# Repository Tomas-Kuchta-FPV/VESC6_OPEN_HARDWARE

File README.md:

# VESC6_OPEN_HARDWARE
> WiP Stage: Designed (asked for funding)  
Open source powerfull VESC that has 2 channels and it's based on the VESC 6 schematic.  

## Design
* 2 channels connected through CAN
* 4 layered PCB
* Continuous current: 70A per ch; instantaneous current: 120A (With proper heat sinking)
* STL130N6F7 MOSFETs rated to switch up to 130A, software limits it to 120A.
* Voltage: 10V-60V(Cells: 3-13S)
* Ports: USB-C, CAN x2, ADC, on/off switch, SWD, Hall Sensors
* LSM6DS3 IMU
* JST-SH connectors (6pin and 4 pin)
* Holes either side of the MOSFETs allow for even clamping of a simple rectangular heatsink.

Possible future upgrades with built in ESP for VESC express.  

## Manufacture
* Commonly usable and easy to source components so you can either have JLCPCB make it for you or assemble it youself.
* Custom board software build as well as hardware configuration files are available in the software folder.
  * Further testing required once I assemble it

## Credits
https://github.com/craigg96/VESC6_OPEN_HARDWARE  

## Motivation
So I love hoverboard motors, but it turns up that a lot of the ESCs are not compatible with the custom FW. And at the end of summer holidays I've designed Hover Cruiser. It's an electric skateboard made out of hoverboard motors. And also my brother made his own gocart powered by hoverboard motors. So thats why I made this modification for 2 channels.  

## BOM
| Item                       | Price          |
| -------------------------- | -------------- |
| LCSC                       | $114.67        |
| LCSC Shipping              | $13.24         |
| LCSC Tarif                 | $38.85         |
| JLCPCB                     | $38.42         |
| JLCPCB Shipping            | $11.86         |
| JLCPCB tarif               | $21.76         |
| Assembly & other materials | Freeeee labor! |
| Total                      | $238.80        |

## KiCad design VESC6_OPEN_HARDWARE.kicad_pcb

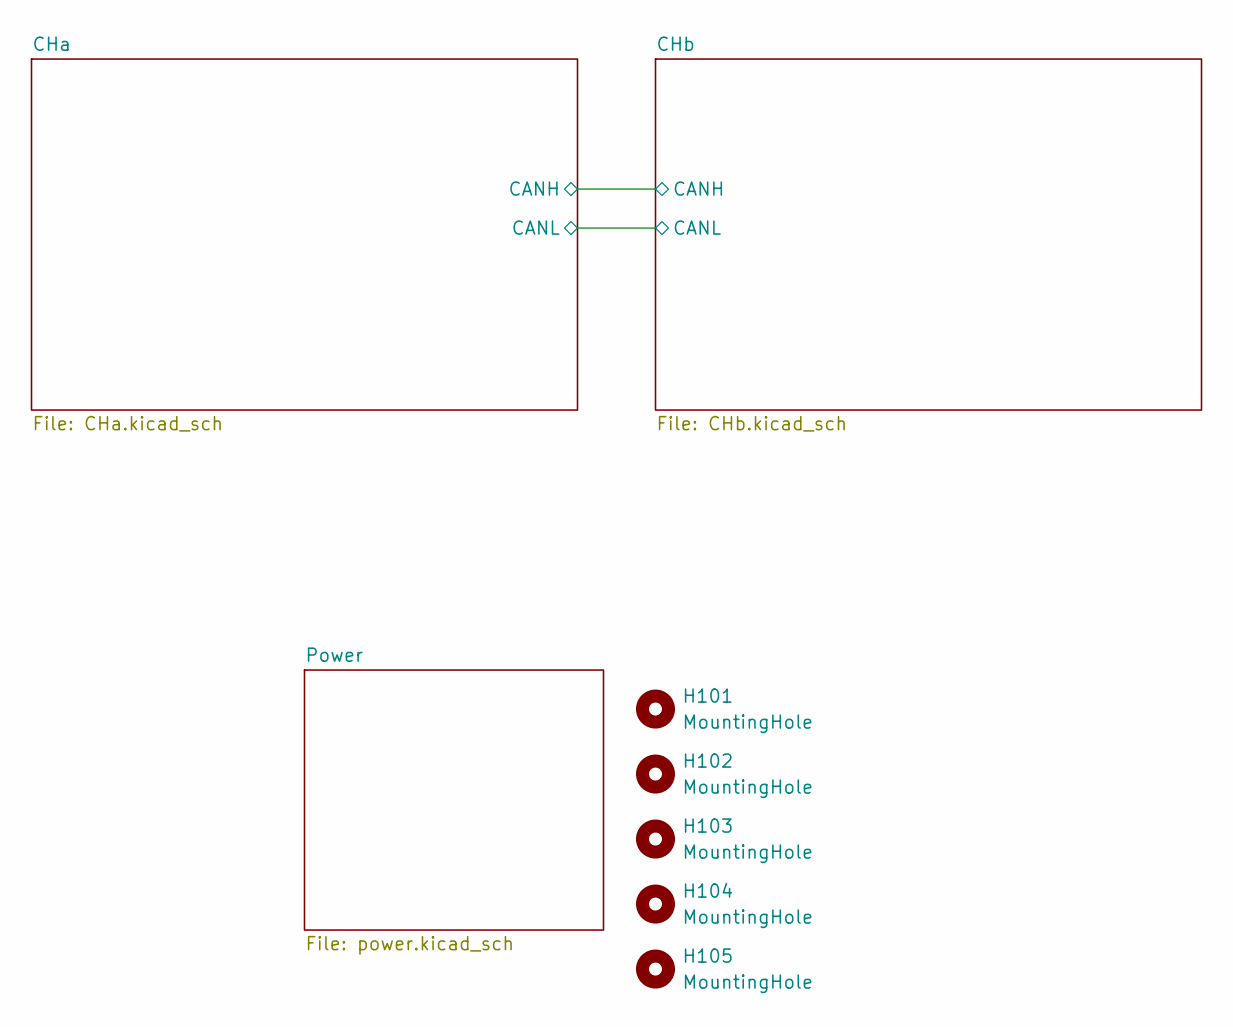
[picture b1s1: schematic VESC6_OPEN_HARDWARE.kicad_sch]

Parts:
H101, H102, H103, H104, H105: MountingHole; MountingHole_3mm

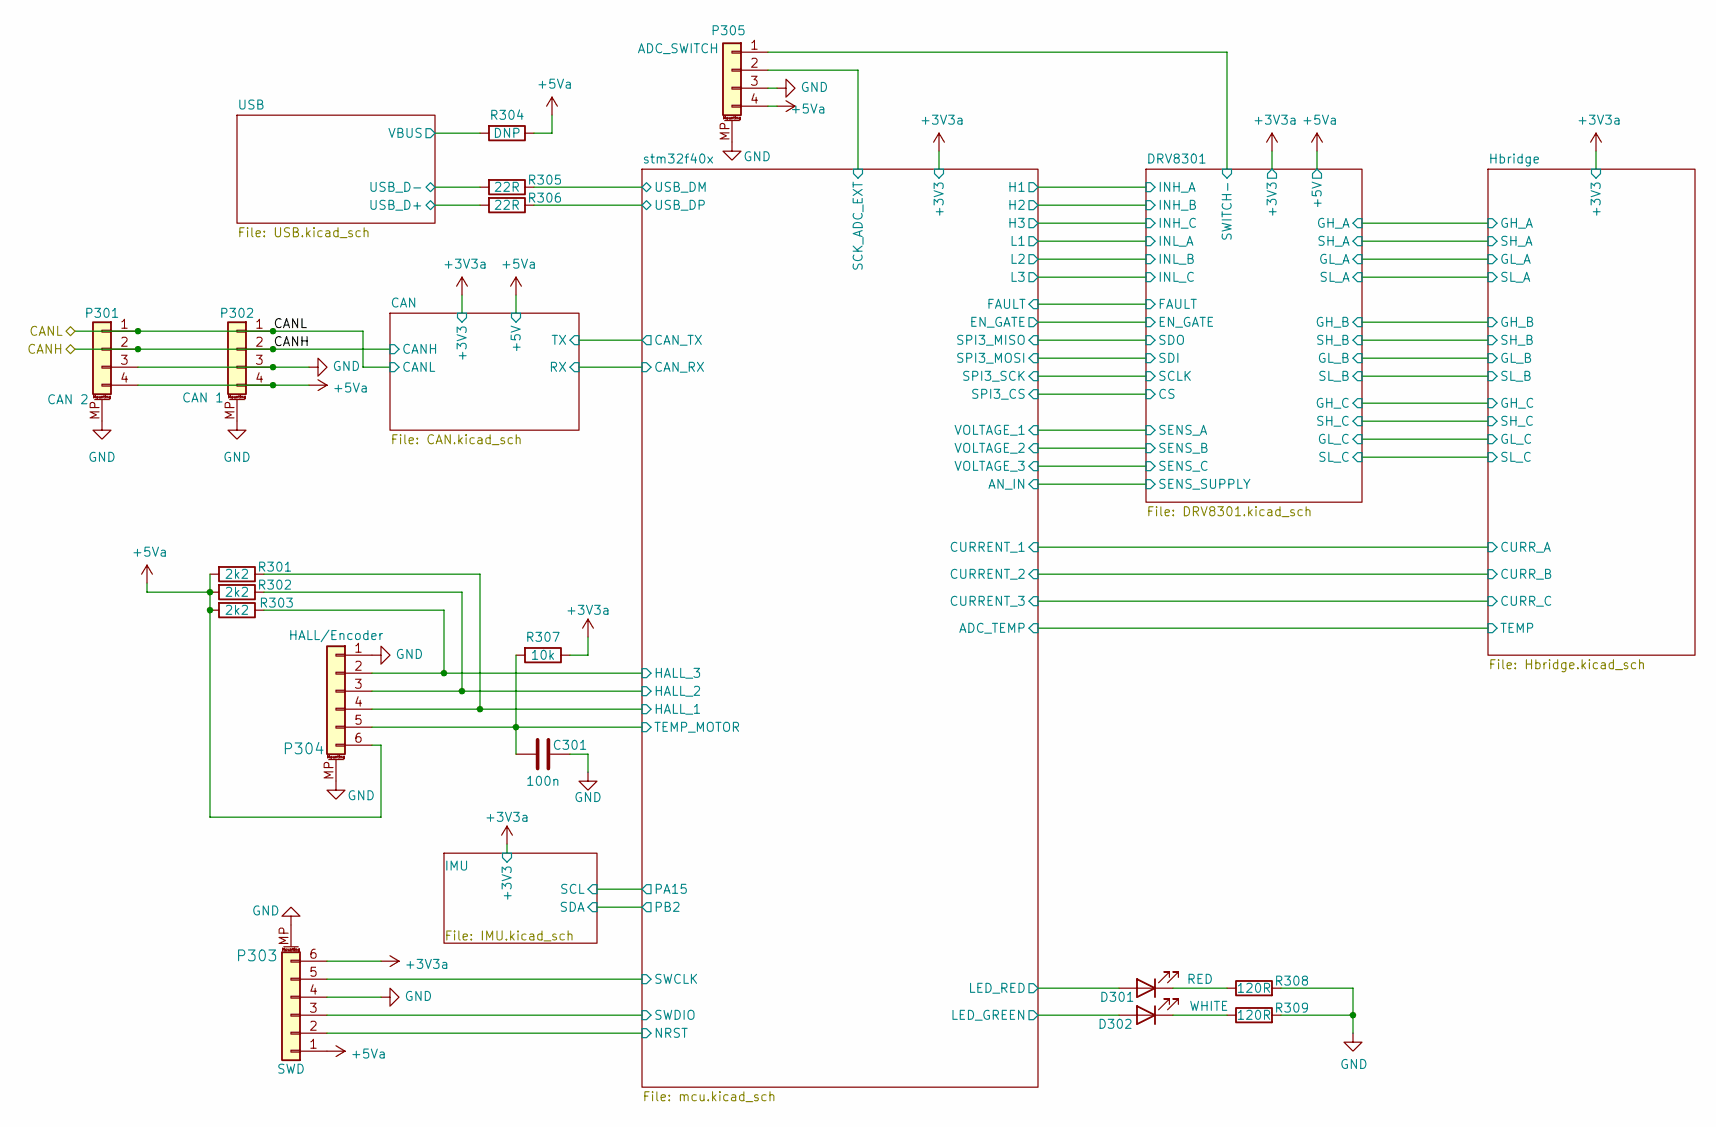
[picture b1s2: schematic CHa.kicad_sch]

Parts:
C301: 100n; C_0603_1608Metric; LCSC C14663
D301: RED; D_0603_1608Metric; LCSC C2286
D302: WHITE; D_0603_1608Metric; LCSC C2290
P301: CAN 2; JST_SH_SM04B-SRSS-TB_1x04-1MP_P1.00mm_Horizontal; LCSC C160404
P302: CAN 1; JST_SH_SM04B-SRSS-TB_1x04-1MP_P1.00mm_Horizontal; LCSC C160404
P303: SWD; JST_SH_SM06B-SRSS-TB_1x06-1MP_P1.00mm_Horizontal; LCSC C160405
P304: HALL/Encoder; JST_SH_SM06B-SRSS-TB_1x06-1MP_P1.00mm_Horizontal; LCSC C160405
P305: ADC_SWITCH; JST_SH_SM04B-SRSS-TB_1x04-1MP_P1.00mm_Horizontal; LCSC C160404
R301, R302, R303: 2k2; R_0603_1608Metric; LCSC C4190
R304: DNP; R_0603_1608Metric
R305, R306: 22R; R_0603_1608Metric; LCSC C23345
R307: 10k; R_0603_1608Metric; LCSC C25804
R308, R309: 120R; R_0603_1608Metric; LCSC C22787

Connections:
+3V3a: P303.6, R307.1; also elsewhere on the board
+5Va: P301.4, P302.4, P303.1, P304.6, P305.4, R301.2, R302.2, R303.2, R304.1; also elsewhere on the board
/CHa/CANH: P301.2, P302.2; also elsewhere on the board
/CHa/CANL: P301.1, P302.1; also elsewhere on the board
/CHa/DRV8301/SWITCH-: P305.1; also elsewhere on the board
/CHa/USB/USB_D+: R306.2; also elsewhere on the board
/CHa/USB/USB_D-: R305.2; also elsewhere on the board
/CHa/USB/VBUS: R304.2; also elsewhere on the board
/CHa/stm32f40x/HALL_1: P304.4, R301.1; also elsewhere on the board
/CHa/stm32f40x/HALL_2: P304.3, R302.1; also elsewhere on the board
/CHa/stm32f40x/HALL_3: P304.2, R303.1; also elsewhere on the board
/CHa/stm32f40x/LED_GREEN: D302.2 (A); also elsewhere on the board
/CHa/stm32f40x/LED_RED: D301.2 (A); also elsewhere on the board
/CHa/stm32f40x/NRST: P303.2; also elsewhere on the board
/CHa/stm32f40x/SCK_ADC_EXT: P305.2; also elsewhere on the board
/CHa/stm32f40x/SWCLK: P303.5; also elsewhere on the board
/CHa/stm32f40x/SWDIO: P303.3; also elsewhere on the board
/CHa/stm32f40x/TEMP_MOTOR: C301.2, P304.5, R307.2; also elsewhere on the board
/CHa/stm32f40x/USB_DM: R305.1; also elsewhere on the board
/CHa/stm32f40x/USB_DP: R306.1; also elsewhere on the board
GND: C301.1, P301.3, P301.MP (MountPin), P302.3, P302.MP (MountPin), P303.4, P303.MP (MountPin), P304.1, P304.MP (MountPin), P305.3, P305.MP (MountPin), R308.2, R309.2; also elsewhere on the board
unnamed: D301.1 (K), R308.1
unnamed: D302.1 (K), R309.1

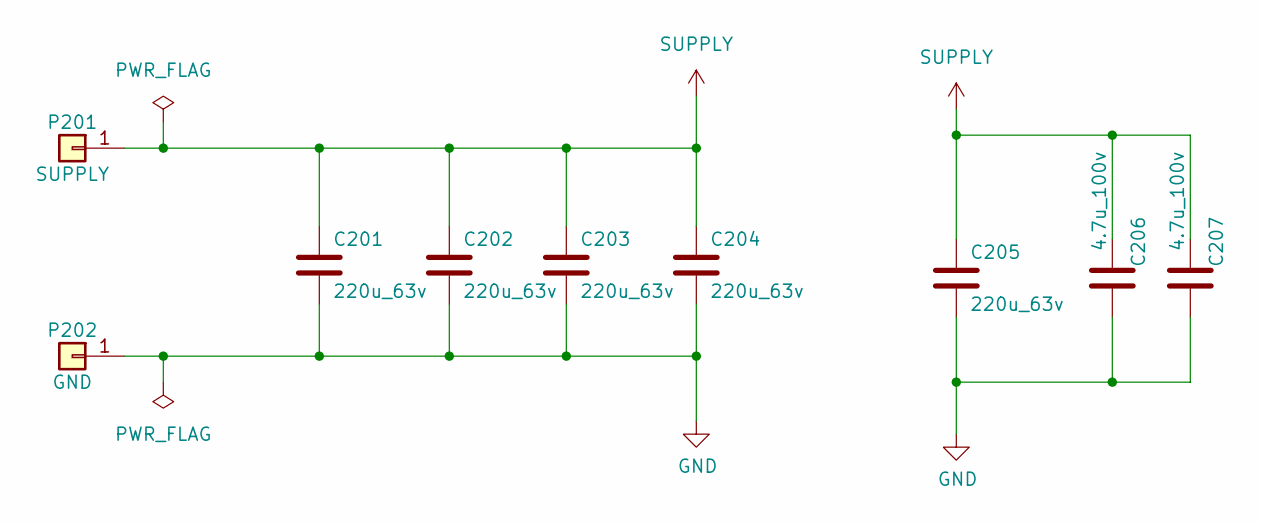
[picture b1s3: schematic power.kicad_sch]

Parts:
C201, C202, C203, C204, C205: 220u_63v; CP_Elec_10x10.5; LCSC C7471900
C206, C207: 4.7u_100v; C_1210_3225Metric; LCSC C385987
P201: SUPPLY; Pin_D1.3mm_L11.0mm_LooseFit; LCSC C7200700
P202: GND; Pin_D1.3mm_L11.0mm_LooseFit; LCSC C7200700

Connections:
GND: C201.2, C202.2, C203.2, C204.2, C205.2, C206.2, C207.2, P202.1 (Pin_1_1); also elsewhere on the board
SUPPLY: C201.1, C202.1, C203.1, C204.1, C205.1, C206.1, C207.1, P201.1 (Pin_1_1); also elsewhere on the board

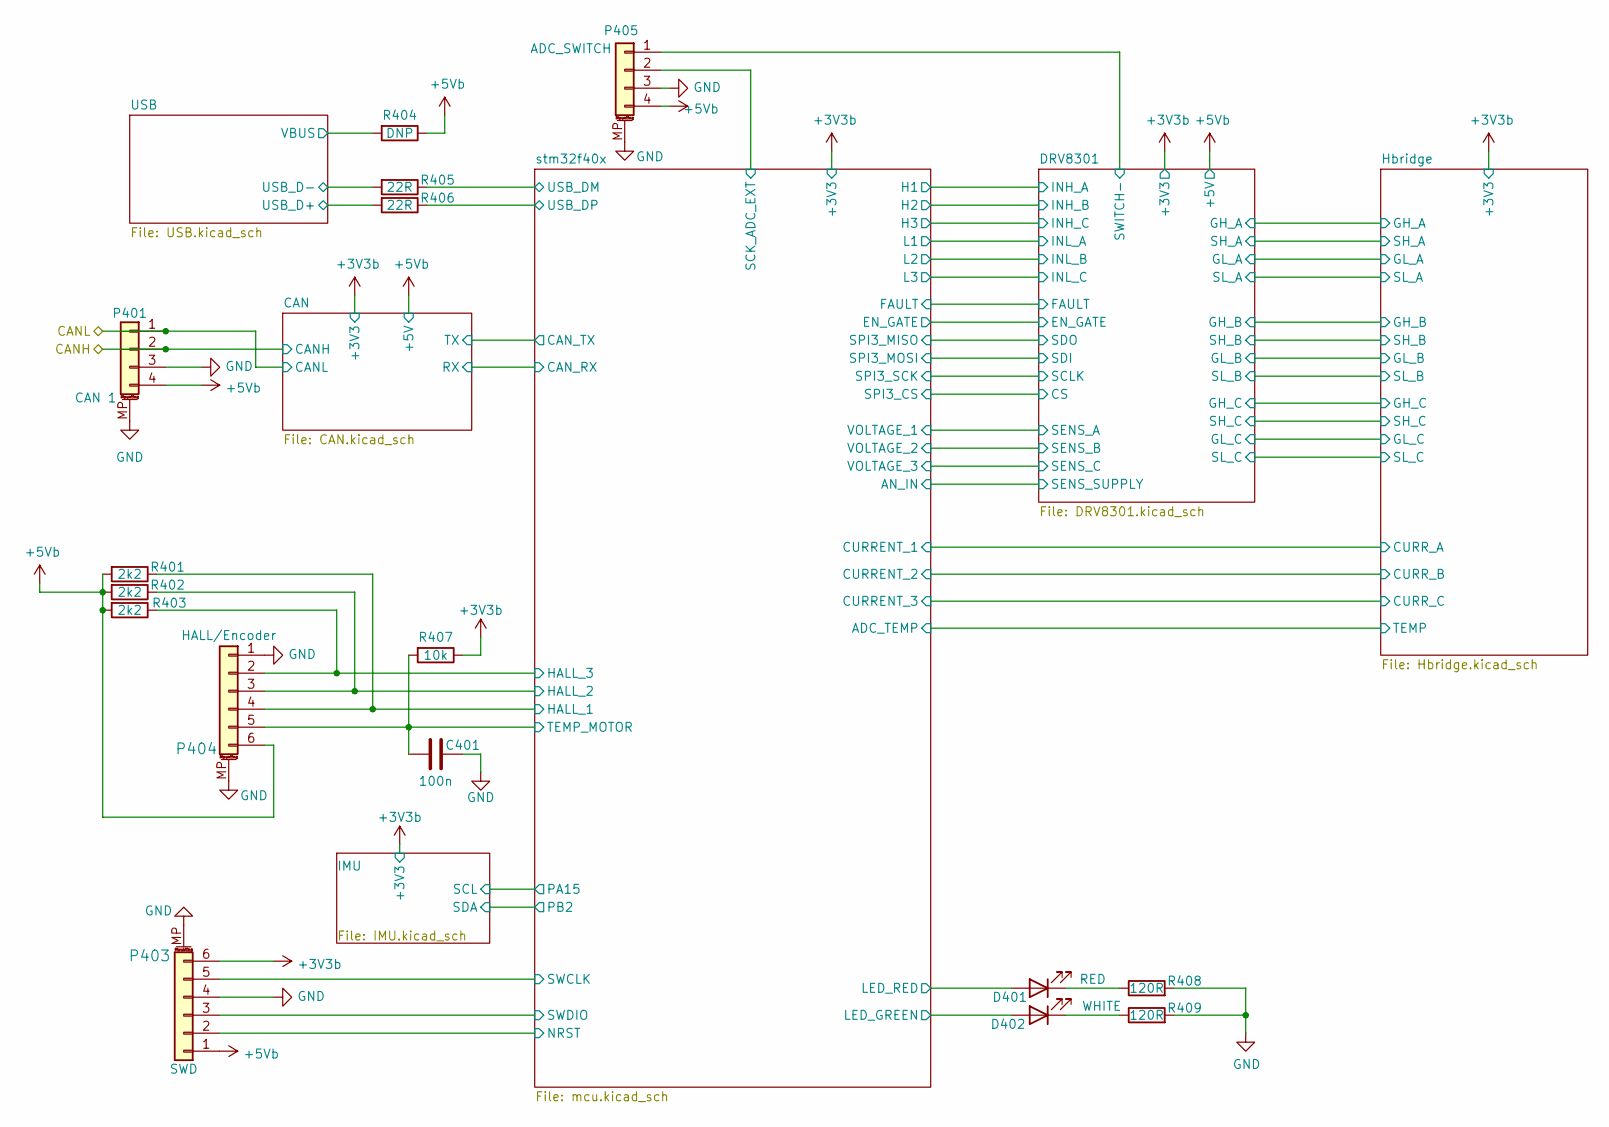
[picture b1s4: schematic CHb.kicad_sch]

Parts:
C401: 100n; C_0603_1608Metric; LCSC C14663
D401: RED; D_0603_1608Metric; LCSC C2286
D402: WHITE; D_0603_1608Metric; LCSC C2290
P401: CAN 1; JST_SH_BM04B-SRSS-TB_1x04-1MP_P1.00mm_Vertical; LCSC C160390
P403: SWD; JST_SH_BM06B-SRSS-TB_1x06-1MP_P1.00mm_Vertical; LCSC C160392
P404: HALL/Encoder; JST_SH_SM06B-SRSS-TB_1x06-1MP_P1.00mm_Horizontal; LCSC C160405
P405: ADC_SWITCH; JST_SH_BM04B-SRSS-TB_1x04-1MP_P1.00mm_Vertical; LCSC C160390
R401, R402, R403: 2k2; R_0603_1608Metric; LCSC C4190
R404: DNP; R_0603_1608Metric
R405, R406: 22R; R_0603_1608Metric; LCSC C23345
R407: 10k; R_0603_1608Metric; LCSC C25804
R408, R409: 120R; R_0603_1608Metric; LCSC C22787

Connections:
+3V3b: P403.6, R407.1; also elsewhere on the board
+5Vb: P401.4, P403.1, P404.6, P405.4, R401.2, R402.2, R403.2, R404.1; also elsewhere on the board
/CHa/CANH: P401.2; also elsewhere on the board
/CHa/CANL: P401.1; also elsewhere on the board
/CHb/DRV8301/SWITCH-: P405.1; also elsewhere on the board
/CHb/USB/USB_D+: R406.2; also elsewhere on the board
/CHb/USB/USB_D-: R405.2; also elsewhere on the board
/CHb/USB/VBUS: R404.2; also elsewhere on the board
/CHb/stm32f40x/HALL_1: P404.4, R401.1; also elsewhere on the board
/CHb/stm32f40x/HALL_2: P404.3, R402.1; also elsewhere on the board
/CHb/stm32f40x/HALL_3: P404.2, R403.1; also elsewhere on the board
/CHb/stm32f40x/LED_GREEN: D402.2 (A); also elsewhere on the board
/CHb/stm32f40x/LED_RED: D401.2 (A); also elsewhere on the board
/CHb/stm32f40x/NRST: P403.2; also elsewhere on the board
/CHb/stm32f40x/SCK_ADC_EXT: P405.2; also elsewhere on the board
/CHb/stm32f40x/SWCLK: P403.5; also elsewhere on the board
/CHb/stm32f40x/SWDIO: P403.3; also elsewhere on the board
/CHb/stm32f40x/TEMP_MOTOR: C401.2, P404.5, R407.2; also elsewhere on the board
/CHb/stm32f40x/USB_DM: R405.1; also elsewhere on the board
/CHb/stm32f40x/USB_DP: R406.1; also elsewhere on the board
GND: C401.1, P401.3, P401.MP (MountPin), P403.4, P403.MP (MountPin), P404.1, P404.MP (MountPin), P405.3, P405.MP (MountPin), R408.2, R409.2; also elsewhere on the board
unnamed: D401.1 (K), R408.1
unnamed: D402.1 (K), R409.1

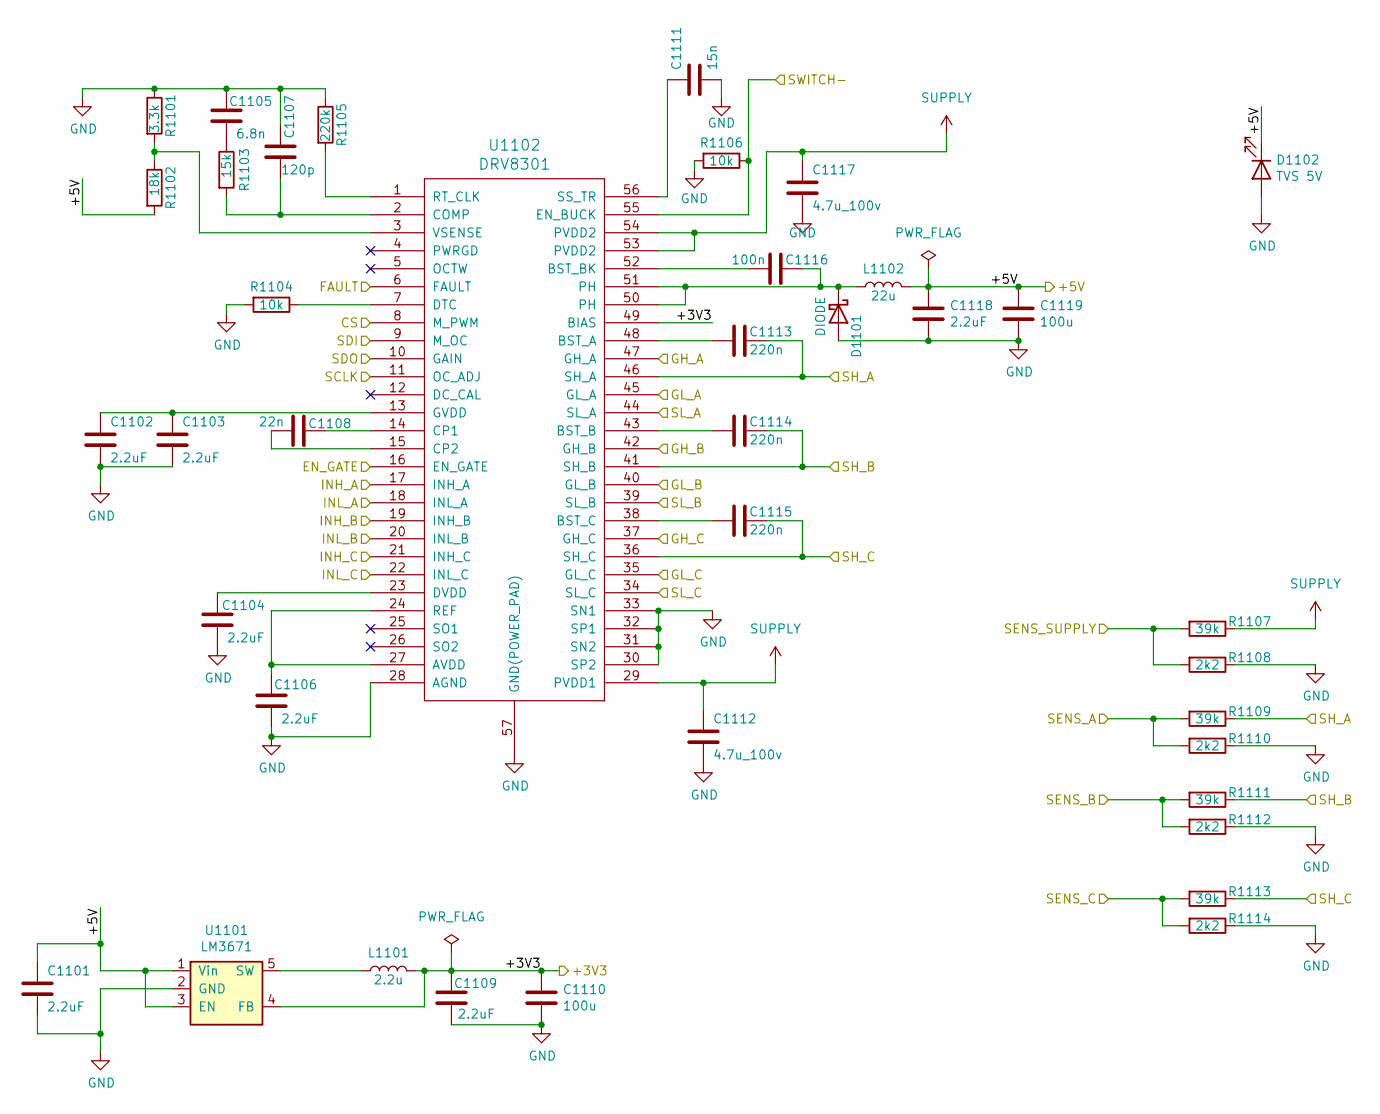
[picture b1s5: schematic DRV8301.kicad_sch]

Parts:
C1101, C1102, C1103, C1104, C1106, C1109, C1118: 2.2uF; C_0603_1608Metric; LCSC C23630
C1105: 6.8n; C_0603_1608Metric; LCSC C1631
C1107: 120p; C_0603_1608Metric; LCSC C107035
C1108: 22n; C_0603_1608Metric; LCSC C21122
C1110, C1119: 100u; C_1210_3225Metric; LCSC C16133
C1111: 15n; C_0603_1608Metric; LCSC C1596
C1112, C1117: 4.7u_100v; C_1210_3225Metric; LCSC C385987
C1113, C1114, C1115: 220n; C_0603_1608Metric; LCSC C21120
C1116: 100n; C_0603_1608Metric; LCSC C14663
D1101: DIODE; D_SMF; LCSC C2923951
D1102: TVS 5V; D_SMA; LCSC C129544
L1101: 2.2u; L_0805_2012Metric; LCSC C383398
L1102: 22u; L_Taiyo-Yuden_NR-60xx_HandSoldering; LCSC C266430
R1101: 3.3k; R_0603_1608Metric; LCSC C22978
R1102: 18k; R_0603_1608Metric; LCSC C25810
R1103: 15k; R_0603_1608Metric; LCSC C22809
R1104, R1106: 10k; R_0603_1608Metric; LCSC C25804
R1105: 220k; R_0603_1608Metric; LCSC C22961
R1107, R1109, R1111, R1113: 39k; R_0603_1608Metric; LCSC C23153
R1108, R1110, R1112, R1114: 2k2; R_0603_1608Metric; LCSC C4190
U1101: LM3671; SOT-23-5; LCSC C477918
U1102: DRV8301; HTSSOP-56-1EP_6.1x14mm_P0.5mm_EP3.61x6.35mm; LCSC C98969

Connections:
+3V3a: C1109.1, C1110.1, L1101.2, U1101.4 (FB), U1102.49 (BIAS); also elsewhere on the board
+5Va: C1101.1, C1118.1, C1119.1, D1102.1 (K), L1102.2, R1102.2, U1101.1 (Vin), U1101.3 (EN); also elsewhere on the board
/CHa/DRV8301/CS: U1102.8 (M_PWM); also elsewhere on the board
/CHa/DRV8301/EN_GATE: U1102.16 (EN_GATE); also elsewhere on the board
/CHa/DRV8301/FAULT: U1102.6 (FAULT); also elsewhere on the board
/CHa/DRV8301/GH_A: U1102.47 (GH_A); also elsewhere on the board
/CHa/DRV8301/GH_B: U1102.42 (GH_B); also elsewhere on the board
/CHa/DRV8301/GH_C: U1102.37 (GH_C); also elsewhere on the board
/CHa/DRV8301/GL_A: U1102.45 (GL_A); also elsewhere on the board
/CHa/DRV8301/GL_B: U1102.40 (GL_B); also elsewhere on the board
/CHa/DRV8301/GL_C: U1102.35 (GL_C); also elsewhere on the board
/CHa/DRV8301/INH_A: U1102.17 (INH_A); also elsewhere on the board
/CHa/DRV8301/INH_B: U1102.19 (INH_B); also elsewhere on the board
/CHa/DRV8301/INH_C: U1102.21 (INH_C); also elsewhere on the board
/CHa/DRV8301/INL_A: U1102.18 (INL_A); also elsewhere on the board
/CHa/DRV8301/INL_B: U1102.20 (INL_B); also elsewhere on the board
/CHa/DRV8301/INL_C: U1102.22 (INL_C); also elsewhere on the board
/CHa/DRV8301/SCLK: U1102.11 (OC_ADJ); also elsewhere on the board
/CHa/DRV8301/SDI: U1102.9 (M_OC); also elsewhere on the board
/CHa/DRV8301/SDO: U1102.10 (GAIN); also elsewhere on the board
/CHa/DRV8301/SENS_A: R1109.2, R1110.2; also elsewhere on the board
/CHa/DRV8301/SENS_B: R1111.2, R1112.2; also elsewhere on the board
/CHa/DRV8301/SENS_C: R1113.2, R1114.2; also elsewhere on the board
/CHa/DRV8301/SENS_SUPPLY: R1107.2, R1108.2; also elsewhere on the board
/CHa/DRV8301/SH_A: C1113.1, R1109.1, U1102.46 (SH_A); also elsewhere on the board
/CHa/DRV8301/SH_B: C1114.1, R1111.1, U1102.41 (SH_B); also elsewhere on the board
/CHa/DRV8301/SH_C: C1115.1, R1113.1, U1102.36 (SH_C); also elsewhere on the board
/CHa/DRV8301/SWITCH-: R1106.1, U1102.55 (EN_BUCK); also elsewhere on the board
GND: C1101.2, C1102.2, C1103.2, C1104.2, C1105.1, C1106.2, C1107.1, C1109.2, C1110.2, C1111.2, C1112.2, C1117.2, C1118.2, C1119.2, D1101.2 (A), D1102.2 (A), R1101.1, R1104.2, R1105.1, R1106.2, R1108.1, R1110.1, R1112.1, R1114.1, U1101.2 (GND), U1102.28 (AGND), U1102.30 (SP2), U1102.31 (SN2), U1102.32 (SP1), U1102.33 (SN1), U1102.34 (SL_C), U1102.39 (SL_B), U1102.44 (SL_A), U1102.57 (GND(POWER_PAD)); also elsewhere on the board
unnamed: C1105.2, R1103.1
unnamed: C1116.1, D1101.1 (K), L1102.1, U1102.50 (PH), U1102.51 (PH)
unnamed: L1101.1, U1101.5 (SW)
unnamed: C1106.1, U1102.24 (REF), U1102.27 (AVDD)
unnamed: C1113.2, U1102.48 (BST_A)
unnamed: C1114.2, U1102.43 (BST_B)
unnamed: C1116.2, U1102.52 (BST_BK)
unnamed: C1115.2, U1102.38 (BST_C)
unnamed: C1107.2, R1103.2, U1102.2 (COMP)
unnamed: C1108.1, U1102.14 (CP1)
unnamed: C1108.2, U1102.15 (CP2)
unnamed: R1104.1, U1102.7 (DTC)
unnamed: C1104.1, U1102.23 (DVDD)
unnamed: C1102.1, C1103.1, U1102.13 (GVDD)
unnamed: R1105.2, U1102.1 (RT_CLK)
unnamed: C1111.1, U1102.56 (SS_TR)
unnamed: R1101.2, R1102.1, U1102.3 (VSENSE)
SUPPLY: C1112.1, C1117.1, R1107.1, U1102.29 (PVDD1), U1102.53 (PVDD2), U1102.54 (PVDD2); also elsewhere on the board

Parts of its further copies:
C2101, C2102, C2103, C2104, C2106, C2109, C2118: 2.2uF; C_0603_1608Metric; LCSC C23630
C2105: 6.8n; C_0603_1608Metric; LCSC C1631
C2107: 120p; C_0603_1608Metric; LCSC C107035
C2108: 22n; C_0603_1608Metric; LCSC C21122
C2110, C2119: 100u; C_1210_3225Metric; LCSC C16133
C2111: 15n; C_0603_1608Metric; LCSC C1596
C2112, C2117: 4.7u_100v; C_1210_3225Metric; LCSC C385987
C2113, C2114, C2115: 220n; C_0603_1608Metric; LCSC C21120
C2116: 100n; C_0603_1608Metric; LCSC C14663
D2101: DIODE; D_SMF; LCSC C2923951
D2102: TVS 5V; D_SMA; LCSC C129544
L2101: 2.2u; L_0805_2012Metric; LCSC C383398
L2102: 22u; L_Taiyo-Yuden_NR-60xx_HandSoldering; LCSC C266430
R2101: 3.3k; R_0603_1608Metric; LCSC C22978
R2102: 18k; R_0603_1608Metric; LCSC C25810
R2103: 15k; R_0603_1608Metric; LCSC C22809
R2104, R2106: 10k; R_0603_1608Metric; LCSC C25804
R2105: 220k; R_0603_1608Metric; LCSC C22961
R2107, R2109, R2111, R2113: 39k; R_0603_1608Metric; LCSC C23153
R2108, R2110, R2112, R2114: 2k2; R_0603_1608Metric; LCSC C4190
U2101: LM3671; SOT-23-5; LCSC C477918
U2102: DRV8301; HTSSOP-56-1EP_6.1x14mm_P0.5mm_EP3.61x6.35mm; LCSC C98969

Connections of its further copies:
+3V3b: C2109.1, C2110.1, L2101.2, U2101.4 (FB), U2102.49 (BIAS); also elsewhere on the board
+5Vb: C2101.1, C2118.1, C2119.1, D2102.1 (K), L2102.2, R2102.2, U2101.1 (Vin), U2101.3 (EN); also elsewhere on the board
/CHb/DRV8301/CS: U2102.8 (M_PWM); also elsewhere on the board
/CHb/DRV8301/EN_GATE: U2102.16 (EN_GATE); also elsewhere on the board
/CHb/DRV8301/FAULT: U2102.6 (FAULT); also elsewhere on the board
/CHb/DRV8301/GH_A: U2102.47 (GH_A); also elsewhere on the board
/CHb/DRV8301/GH_B: U2102.42 (GH_B); also elsewhere on the board
/CHb/DRV8301/GH_C: U2102.37 (GH_C); also elsewhere on the board
/CHb/DRV8301/GL_A: U2102.45 (GL_A); also elsewhere on the board
/CHb/DRV8301/GL_B: U2102.40 (GL_B); also elsewhere on the board
/CHb/DRV8301/GL_C: U2102.35 (GL_C); also elsewhere on the board
/CHb/DRV8301/INH_A: U2102.17 (INH_A); also elsewhere on the board
/CHb/DRV8301/INH_B: U2102.19 (INH_B); also elsewhere on the board
/CHb/DRV8301/INH_C: U2102.21 (INH_C); also elsewhere on the board
/CHb/DRV8301/INL_A: U2102.18 (INL_A); also elsewhere on the board
/CHb/DRV8301/INL_B: U2102.20 (INL_B); also elsewhere on the board
/CHb/DRV8301/INL_C: U2102.22 (INL_C); also elsewhere on the board
/CHb/DRV8301/SCLK: U2102.11 (OC_ADJ); also elsewhere on the board
/CHb/DRV8301/SDI: U2102.9 (M_OC); also elsewhere on the board
/CHb/DRV8301/SDO: U2102.10 (GAIN); also elsewhere on the board
/CHb/DRV8301/SENS_A: R2109.2, R2110.2; also elsewhere on the board
/CHb/DRV8301/SENS_B: R2111.2, R2112.2; also elsewhere on the board
/CHb/DRV8301/SENS_C: R2113.2, R2114.2; also elsewhere on the board
/CHb/DRV8301/SENS_SUPPLY: R2107.2, R2108.2; also elsewhere on the board
/CHb/DRV8301/SH_A: C2113.1, R2109.1, U2102.46 (SH_A); also elsewhere on the board
/CHb/DRV8301/SH_B: C2114.1, R2111.1, U2102.41 (SH_B); also elsewhere on the board
/CHb/DRV8301/SH_C: C2115.1, R2113.1, U2102.36 (SH_C); also elsewhere on the board
/CHb/DRV8301/SWITCH-: R2106.1, U2102.55 (EN_BUCK); also elsewhere on the board
GND: C2101.2, C2102.2, C2103.2, C2104.2, C2105.1, C2106.2, C2107.1, C2109.2, C2110.2, C2111.2, C2112.2, C2117.2, C2118.2, C2119.2, D2101.2 (A), D2102.2 (A), R2101.1, R2104.2, R2105.1, R2106.2, R2108.1, R2110.1, R2112.1, R2114.1, U2101.2 (GND), U2102.28 (AGND), U2102.30 (SP2), U2102.31 (SN2), U2102.32 (SP1), U2102.33 (SN1), U2102.34 (SL_C), U2102.39 (SL_B), U2102.44 (SL_A), U2102.57 (GND(POWER_PAD)); also elsewhere on the board
unnamed: C2105.2, R2103.1
unnamed: C2116.1, D2101.1 (K), L2102.1, U2102.50 (PH), U2102.51 (PH)
unnamed: L2101.1, U2101.5 (SW)
unnamed: C2106.1, U2102.24 (REF), U2102.27 (AVDD)
unnamed: C2113.2, U2102.48 (BST_A)
unnamed: C2114.2, U2102.43 (BST_B)
unnamed: C2116.2, U2102.52 (BST_BK)
unnamed: C2115.2, U2102.38 (BST_C)
unnamed: C2107.2, R2103.2, U2102.2 (COMP)
unnamed: C2108.1, U2102.14 (CP1)
unnamed: C2108.2, U2102.15 (CP2)
unnamed: R2104.1, U2102.7 (DTC)
unnamed: C2104.1, U2102.23 (DVDD)
unnamed: C2102.1, C2103.1, U2102.13 (GVDD)
unnamed: R2105.2, U2102.1 (RT_CLK)
unnamed: C2111.1, U2102.56 (SS_TR)
unnamed: R2101.2, R2102.1, U2102.3 (VSENSE)
SUPPLY: C2112.1, C2117.1, R2107.1, U2102.29 (PVDD1), U2102.53 (PVDD2), U2102.54 (PVDD2); also elsewhere on the board

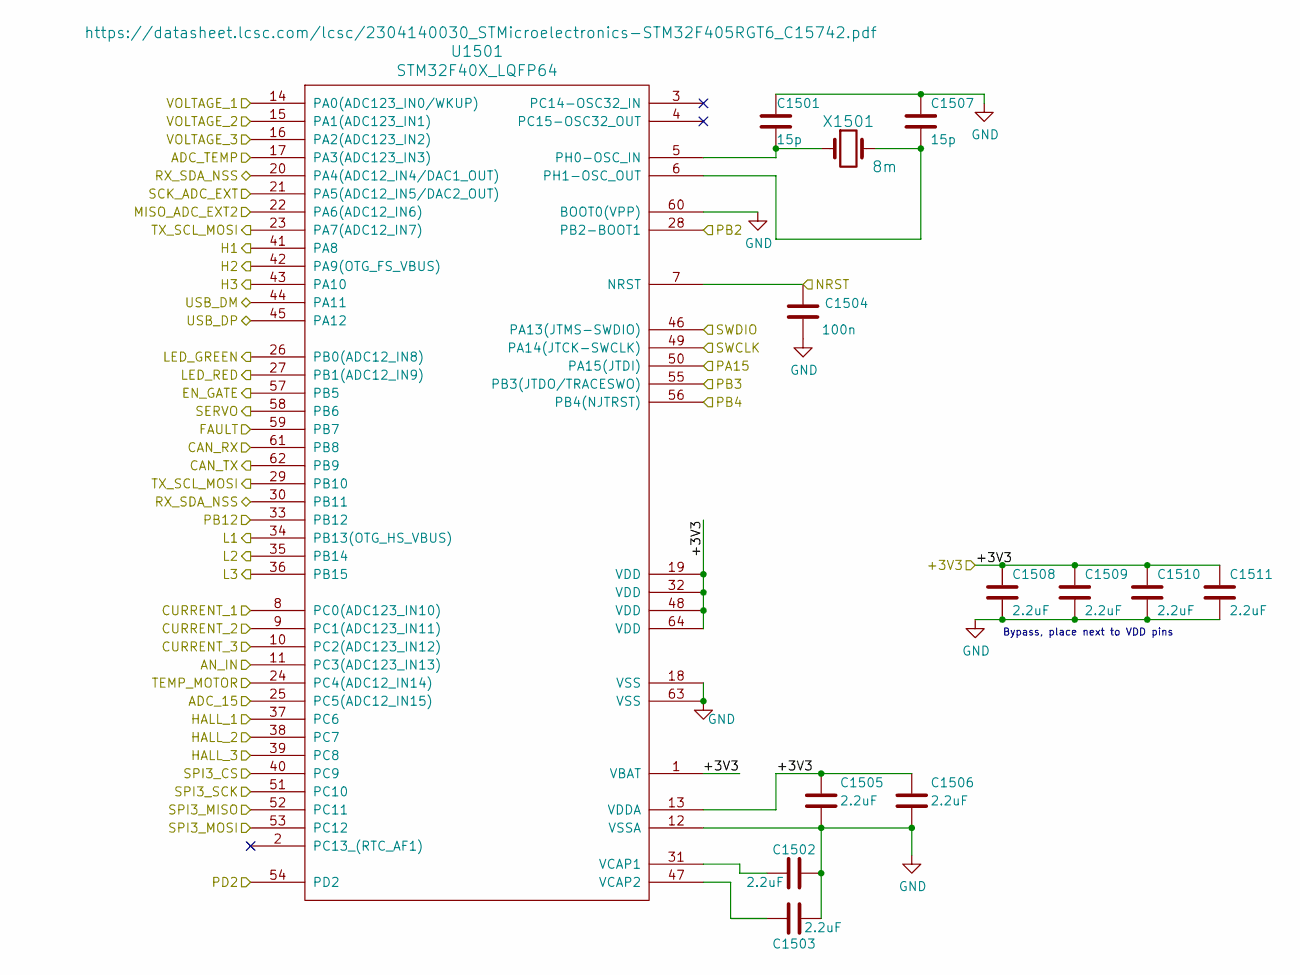
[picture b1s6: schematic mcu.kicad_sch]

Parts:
C1501, C1507: 15p; C_0603_1608Metric; LCSC C1644
C1502, C1503, C1505, C1506, C1508, C1509, C1510, C1511: 2.2uF; C_0603_1608Metric; LCSC C23630
C1504: 100n; C_0603_1608Metric; LCSC C14663
U1501: STM32F40X_LQFP64; LQFP-64_10x10mm_P0.5mm; LCSC C15742
X1501: 8m; Crystal_SMD_5032-2Pin_5.0x3.2mm; LCSC C115962

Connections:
+3V3a: C1505.1, C1506.1, C1508.1, C1509.1, C1510.1, C1511.1, U1501.1 (VBAT), U1501.13 (VDDA), U1501.19 (VDD), U1501.32 (VDD), U1501.48 (VDD), U1501.64 (VDD); also elsewhere on the board
/CHa/CAN/RX: U1501.61 (PB8); also elsewhere on the board
/CHa/CAN/TX: U1501.62 (PB9); also elsewhere on the board
/CHa/DRV8301/CS: U1501.40 (PC9); also elsewhere on the board
/CHa/DRV8301/EN_GATE: U1501.57 (PB5); also elsewhere on the board
/CHa/DRV8301/FAULT: U1501.59 (PB7); also elsewhere on the board
/CHa/DRV8301/INH_A: U1501.41 (PA8); also elsewhere on the board
/CHa/DRV8301/INH_B: U1501.42 (PA9(OTG_FS_VBUS)); also elsewhere on the board
/CHa/DRV8301/INH_C: U1501.43 (PA10); also elsewhere on the board
/CHa/DRV8301/INL_A: U1501.34 (PB13(OTG_HS_VBUS)); also elsewhere on the board
/CHa/DRV8301/INL_B: U1501.35 (PB14); also elsewhere on the board
/CHa/DRV8301/INL_C: U1501.36 (PB15); also elsewhere on the board
/CHa/DRV8301/SCLK: U1501.51 (PC10); also elsewhere on the board
/CHa/DRV8301/SDI: U1501.53 (PC12); also elsewhere on the board
/CHa/DRV8301/SDO: U1501.52 (PC11); also elsewhere on the board
/CHa/DRV8301/SENS_A: U1501.14 (PA0(ADC123_IN0/WKUP)); also elsewhere on the board
/CHa/DRV8301/SENS_B: U1501.15 (PA1(ADC123_IN1)); also elsewhere on the board
/CHa/DRV8301/SENS_C: U1501.16 (PA2(ADC123_IN2)); also elsewhere on the board
/CHa/DRV8301/SENS_SUPPLY: U1501.11 (PC3(ADC123_IN13)); also elsewhere on the board
/CHa/Hbridge/CURR_A: U1501.8 (PC0(ADC123_IN10)); also elsewhere on the board
/CHa/Hbridge/CURR_B: U1501.9 (PC1(ADC123_IN11)); also elsewhere on the board
/CHa/Hbridge/CURR_C: U1501.10 (PC2(ADC123_IN12)); also elsewhere on the board
/CHa/Hbridge/TEMP: U1501.17 (PA3(ADC123_IN3)); also elsewhere on the board
/CHa/IMU/SCL: U1501.50 (PA15(JTDI)); also elsewhere on the board
/CHa/IMU/SDA: U1501.28 (PB2-BOOT1); also elsewhere on the board
/CHa/stm32f40x/ADC_15: U1501.25 (PC5(ADC12_IN15))
/CHa/stm32f40x/HALL_1: U1501.37 (PC6); also elsewhere on the board
/CHa/stm32f40x/HALL_2: U1501.38 (PC7); also elsewhere on the board
/CHa/stm32f40x/HALL_3: U1501.39 (PC8); also elsewhere on the board
/CHa/stm32f40x/LED_GREEN: U1501.26 (PB0(ADC12_IN8)); also elsewhere on the board
/CHa/stm32f40x/LED_RED: U1501.27 (PB1(ADC12_IN9)); also elsewhere on the board
/CHa/stm32f40x/MISO_ADC_EXT2: U1501.22 (PA6(ADC12_IN6))
/CHa/stm32f40x/NRST: C1504.1, U1501.7 (NRST); also elsewhere on the board
/CHa/stm32f40x/PB3: U1501.55 (PB3(JTDO/TRACESWO))
/CHa/stm32f40x/PB4: U1501.56 (PB4(NJTRST))
/CHa/stm32f40x/PB12: U1501.33 (PB12)
/CHa/stm32f40x/PD2: U1501.54 (PD2)
/CHa/stm32f40x/RX_SDA_NSS: U1501.20 (PA4(ADC12_IN4/DAC1_OUT)), U1501.30 (PB11)
/CHa/stm32f40x/SCK_ADC_EXT: U1501.21 (PA5(ADC12_IN5/DAC2_OUT)); also elsewhere on the board
/CHa/stm32f40x/SERVO: U1501.58 (PB6)
/CHa/stm32f40x/SWCLK: U1501.49 (PA14(JTCK-SWCLK)); also elsewhere on the board
/CHa/stm32f40x/SWDIO: U1501.46 (PA13(JTMS-SWDIO)); also elsewhere on the board
/CHa/stm32f40x/TEMP_MOTOR: U1501.24 (PC4(ADC12_IN14)); also elsewhere on the board
/CHa/stm32f40x/TX_SCL_MOSI: U1501.23 (PA7(ADC12_IN7)), U1501.29 (PB10)
/CHa/stm32f40x/USB_DM: U1501.44 (PA11); also elsewhere on the board
/CHa/stm32f40x/USB_DP: U1501.45 (PA12); also elsewhere on the board
GND: C1501.1, C1502.1, C1503.1, C1504.2, C1505.2, C1506.2, C1507.1, C1508.2, C1509.2, C1510.2, C1511.2, U1501.12 (VSSA), U1501.18 (VSS), U1501.60 (BOOT0(VPP)), U1501.63 (VSS); also elsewhere on the board
unnamed: C1501.2, U1501.5 (PH0-OSC_IN), X1501.1
unnamed: C1507.2, U1501.6 (PH1-OSC_OUT), X1501.2
unnamed: C1502.2, U1501.31 (VCAP1)
unnamed: C1503.2, U1501.47 (VCAP2)

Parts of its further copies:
C2501, C2507: 15p; C_0603_1608Metric; LCSC C1644
C2502, C2503, C2505, C2506, C2508, C2509, C2510, C2511: 2.2uF; C_0603_1608Metric; LCSC C23630
C2504: 100n; C_0603_1608Metric; LCSC C14663
U2501: STM32F40X_LQFP64; LQFP-64_10x10mm_P0.5mm; LCSC C15742
X2501: 8m; Crystal_SMD_5032-2Pin_5.0x3.2mm; LCSC C115962

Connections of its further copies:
+3V3b: C2505.1, C2506.1, C2508.1, C2509.1, C2510.1, C2511.1, U2501.1 (VBAT), U2501.13 (VDDA), U2501.19 (VDD), U2501.32 (VDD), U2501.48 (VDD), U2501.64 (VDD); also elsewhere on the board
/CHb/CAN/RX: U2501.61 (PB8); also elsewhere on the board
/CHb/CAN/TX: U2501.62 (PB9); also elsewhere on the board
/CHb/DRV8301/CS: U2501.40 (PC9); also elsewhere on the board
/CHb/DRV8301/EN_GATE: U2501.57 (PB5); also elsewhere on the board
/CHb/DRV8301/FAULT: U2501.59 (PB7); also elsewhere on the board
/CHb/DRV8301/INH_A: U2501.41 (PA8); also elsewhere on the board
/CHb/DRV8301/INH_B: U2501.42 (PA9(OTG_FS_VBUS)); also elsewhere on the board
/CHb/DRV8301/INH_C: U2501.43 (PA10); also elsewhere on the board
/CHb/DRV8301/INL_A: U2501.34 (PB13(OTG_HS_VBUS)); also elsewhere on the board
/CHb/DRV8301/INL_B: U2501.35 (PB14); also elsewhere on the board
/CHb/DRV8301/INL_C: U2501.36 (PB15); also elsewhere on the board
/CHb/DRV8301/SCLK: U2501.51 (PC10); also elsewhere on the board
/CHb/DRV8301/SDI: U2501.53 (PC12); also elsewhere on the board
/CHb/DRV8301/SDO: U2501.52 (PC11); also elsewhere on the board
/CHb/DRV8301/SENS_A: U2501.14 (PA0(ADC123_IN0/WKUP)); also elsewhere on the board
/CHb/DRV8301/SENS_B: U2501.15 (PA1(ADC123_IN1)); also elsewhere on the board
/CHb/DRV8301/SENS_C: U2501.16 (PA2(ADC123_IN2)); also elsewhere on the board
/CHb/DRV8301/SENS_SUPPLY: U2501.11 (PC3(ADC123_IN13)); also elsewhere on the board
/CHb/Hbridge/CURR_A: U2501.8 (PC0(ADC123_IN10)); also elsewhere on the board
/CHb/Hbridge/CURR_B: U2501.9 (PC1(ADC123_IN11)); also elsewhere on the board
/CHb/Hbridge/CURR_C: U2501.10 (PC2(ADC123_IN12)); also elsewhere on the board
/CHb/Hbridge/TEMP: U2501.17 (PA3(ADC123_IN3)); also elsewhere on the board
/CHb/IMU/SCL: U2501.50 (PA15(JTDI)); also elsewhere on the board
/CHb/IMU/SDA: U2501.28 (PB2-BOOT1); also elsewhere on the board
/CHb/stm32f40x/ADC_15: U2501.25 (PC5(ADC12_IN15))
/CHb/stm32f40x/HALL_1: U2501.37 (PC6); also elsewhere on the board
/CHb/stm32f40x/HALL_2: U2501.38 (PC7); also elsewhere on the board
/CHb/stm32f40x/HALL_3: U2501.39 (PC8); also elsewhere on the board
/CHb/stm32f40x/LED_GREEN: U2501.26 (PB0(ADC12_IN8)); also elsewhere on the board
/CHb/stm32f40x/LED_RED: U2501.27 (PB1(ADC12_IN9)); also elsewhere on the board
/CHb/stm32f40x/MISO_ADC_EXT2: U2501.22 (PA6(ADC12_IN6))
/CHb/stm32f40x/NRST: C2504.1, U2501.7 (NRST); also elsewhere on the board
/CHb/stm32f40x/PB3: U2501.55 (PB3(JTDO/TRACESWO))
/CHb/stm32f40x/PB4: U2501.56 (PB4(NJTRST))
/CHb/stm32f40x/PB12: U2501.33 (PB12)
/CHb/stm32f40x/PD2: U2501.54 (PD2)
/CHb/stm32f40x/RX_SDA_NSS: U2501.20 (PA4(ADC12_IN4/DAC1_OUT)), U2501.30 (PB11)
/CHb/stm32f40x/SCK_ADC_EXT: U2501.21 (PA5(ADC12_IN5/DAC2_OUT)); also elsewhere on the board
/CHb/stm32f40x/SERVO: U2501.58 (PB6)
/CHb/stm32f40x/SWCLK: U2501.49 (PA14(JTCK-SWCLK)); also elsewhere on the board
/CHb/stm32f40x/SWDIO: U2501.46 (PA13(JTMS-SWDIO)); also elsewhere on the board
/CHb/stm32f40x/TEMP_MOTOR: U2501.24 (PC4(ADC12_IN14)); also elsewhere on the board
/CHb/stm32f40x/TX_SCL_MOSI: U2501.23 (PA7(ADC12_IN7)), U2501.29 (PB10)
/CHb/stm32f40x/USB_DM: U2501.44 (PA11); also elsewhere on the board
/CHb/stm32f40x/USB_DP: U2501.45 (PA12); also elsewhere on the board
GND: C2501.1, C2502.1, C2503.1, C2504.2, C2505.2, C2506.2, C2507.1, C2508.2, C2509.2, C2510.2, C2511.2, U2501.12 (VSSA), U2501.18 (VSS), U2501.60 (BOOT0(VPP)), U2501.63 (VSS); also elsewhere on the board
unnamed: C2501.2, U2501.5 (PH0-OSC_IN), X2501.1
unnamed: C2507.2, U2501.6 (PH1-OSC_OUT), X2501.2
unnamed: C2502.2, U2501.31 (VCAP1)
unnamed: C2503.2, U2501.47 (VCAP2)

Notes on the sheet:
Bypass, place next to VDD pins
